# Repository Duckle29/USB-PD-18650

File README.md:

# USB PD 18650

I needed a 12V 5A PSU for my Sequre S60 soldering iron, and I couldn't find any reasonably priced ones, so why not make
my own unreasonably priced one?

This uses an STM32G0 MCU with a TCPP03-M20 protection chip
A MPS programmable buck/boost to provide 5-20V output at up to 5A

The goal is currently to make a complete USB-PD supply with PPS support, but this may be dropped if I don't feel like it when I
figure out how hard it'll be.

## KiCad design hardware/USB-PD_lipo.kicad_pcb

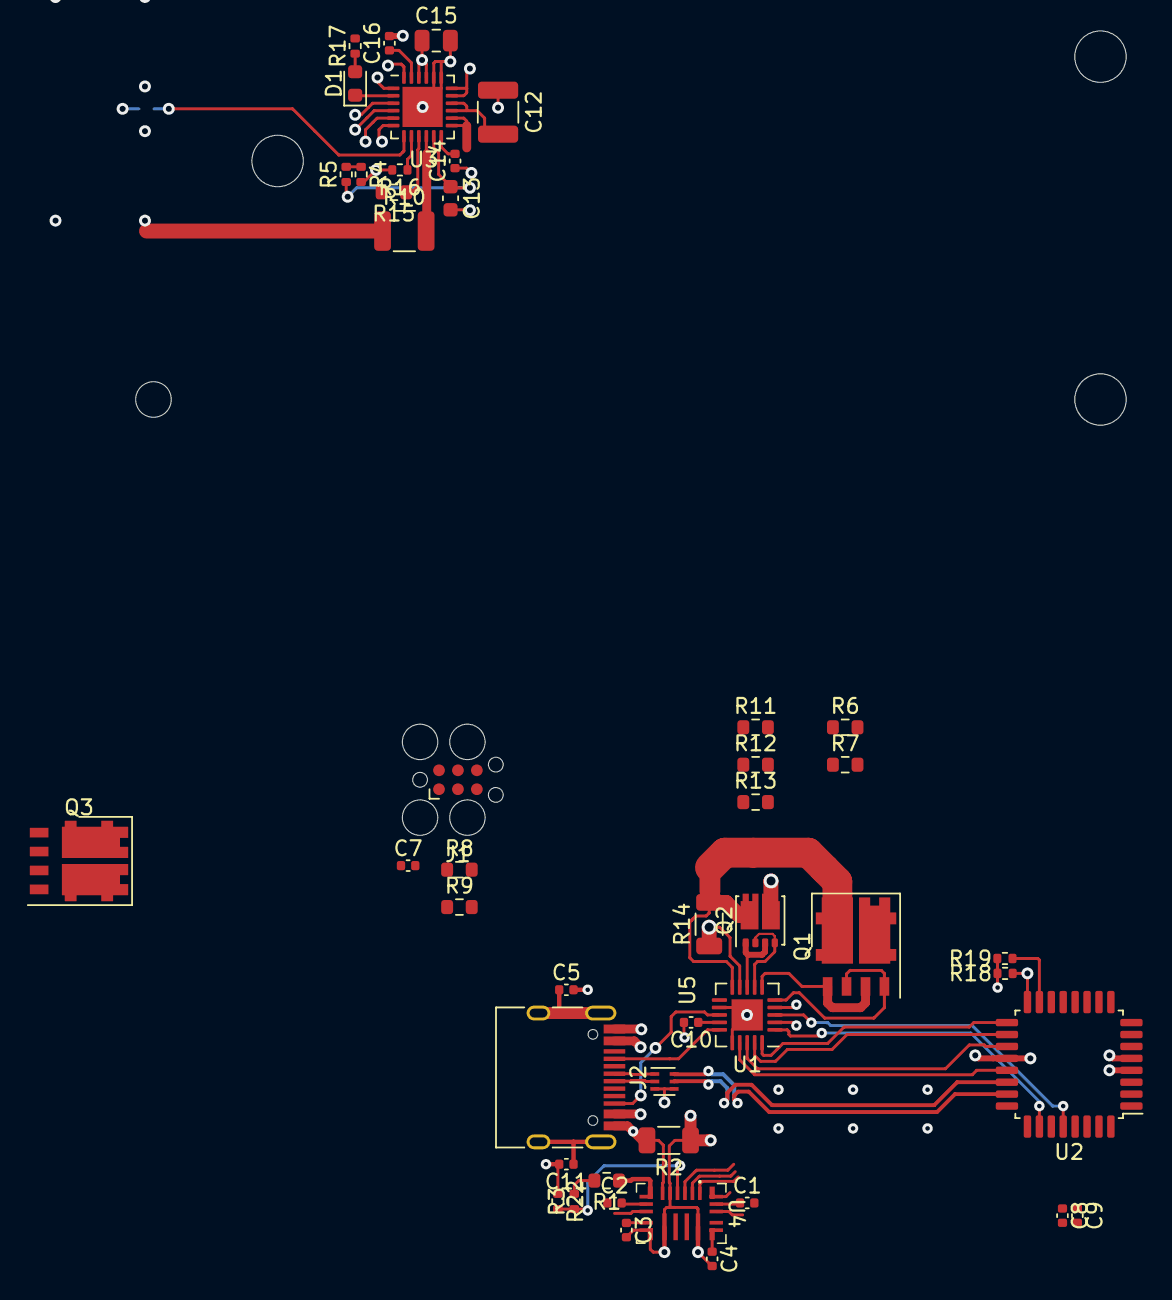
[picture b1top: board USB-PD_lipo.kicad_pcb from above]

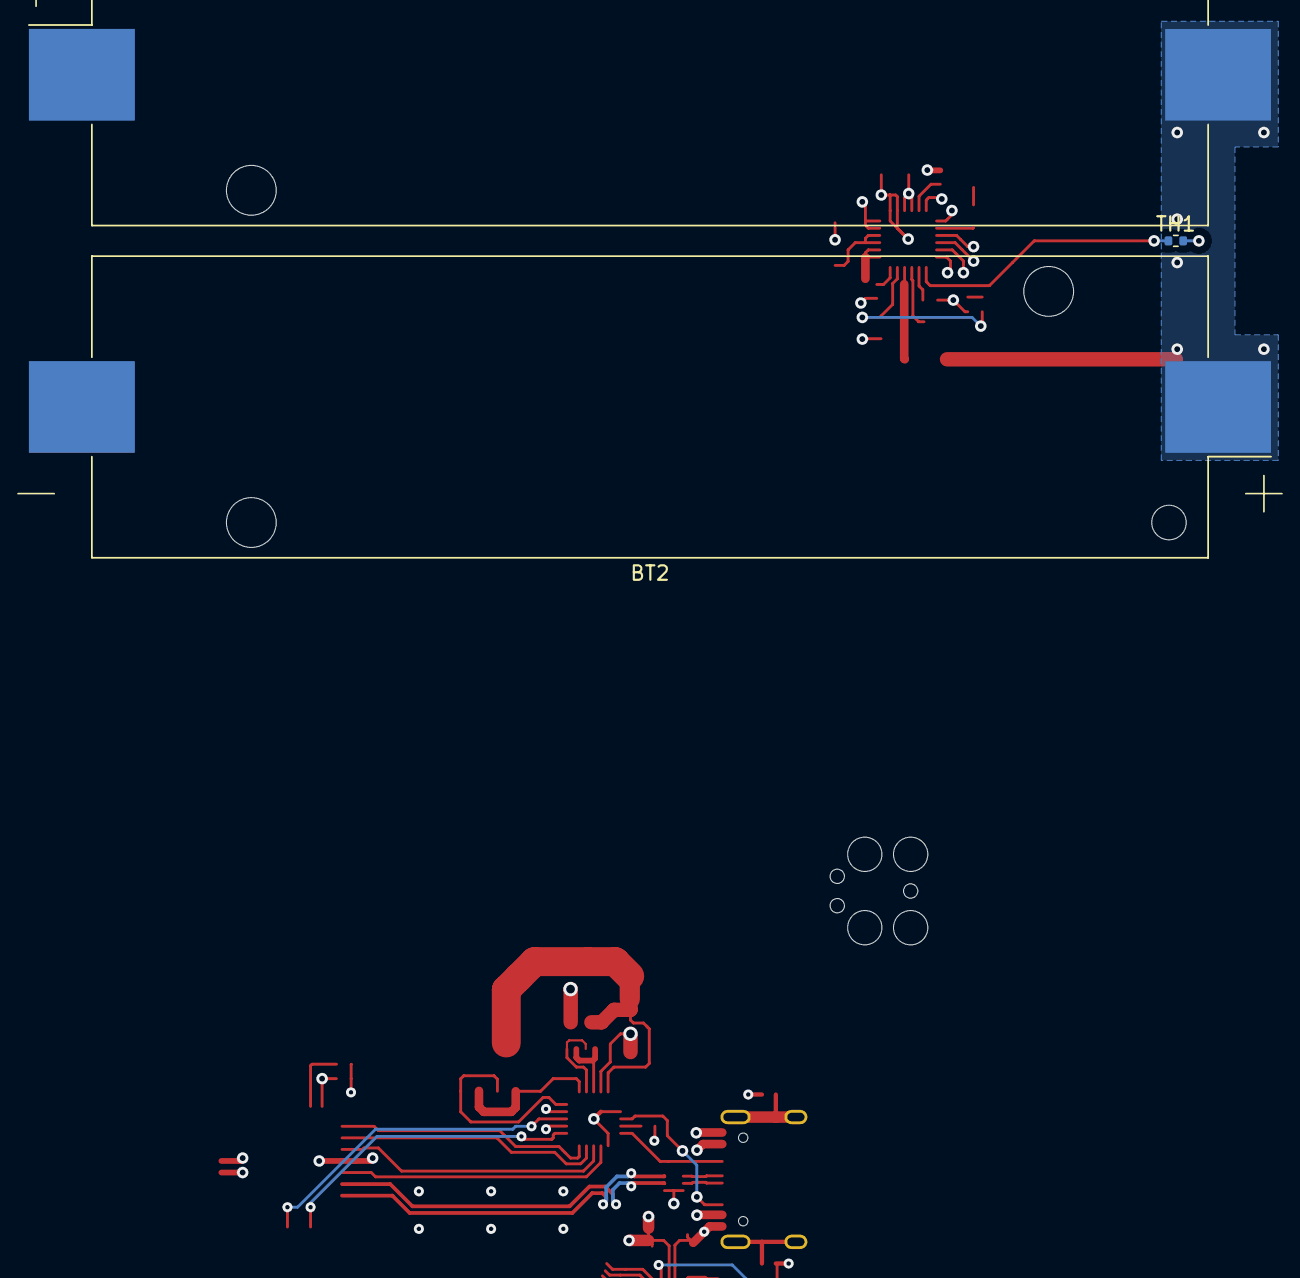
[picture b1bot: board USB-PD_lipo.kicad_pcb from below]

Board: 4 copper layers, 49 parts (3 on the bottom side), 61 nets.

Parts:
BT1, BT2: Battery_Cell; BatteryHolder_Keystone_1042_1x18650
C1, C2: 220nF; C_0402_1005Metric
C3: 1uF; C_0402_1005Metric
C4: 100pF; C_0402_1005Metric
C5, C10, C11: 100nF 50v; C_0402_1005Metric
C7, C8, C9: 100nF; C_0402_1005Metric
C12: 44uF; C_1210_3225Metric
C13: 4u7; C_0603_1608Metric
C14: 47n; C_0402_1005Metric
C15: 10uF; C_0805_2012Metric
C16: 1u; C_0402_1005Metric
D1: LED_Small; LED_0603_1608Metric
J1: TC2030-SWD; Tag-Connect_TC2030-IDC-FP_2x03_P1.27mm_Vertical
J2: USB_C_Receptacle_USB2.0; USB_C_Receptacle_HRO_TYPE-C-31-M-12
Q1, Q3: STL40DN3LLH5; ST_PowerFLAT-6L_5x6mm_P1.27mm
Q2: DMT3020LDV; Diodes_PowerDI3333-8_UXC_3.3x3.3mm_P0.65mm
R1: 3R3; R_0603_1608Metric
R2, R14: 5mR; R_1206_3216Metric
R3: 90k9; R_0402_1005Metric
R4: 30k1; R_0402_1005Metric
R5: 5k23; R_0402_1005Metric
R6, R7, R8, R9, R11: 10k; R_0603_1608Metric
R10: 22R 1W; R_1210_3225Metric
R12, R13: 47k; R_0603_1608Metric
R15: 300R; R_0603_1608Metric
R16: 383R; R_0402_1005Metric
R17: 2k2; R_0402_1005Metric
R18, R19, R22: 10k; R_0402_1005Metric
TH1: 10K beta3435; R_0402_1005Metric
U1: TCPP03-M20; TQFN-20-1EP_4x4mm_P0.5mm_EP2.1x2.1mm
U2: STM32G0C1KETxN; LQFP-32_7x7mm_P0.8mm
U3: BQ25887; QFN-24-1EP_4x4mm_P0.5mm_EP2.7x2.7mm
U4: MP4247; MPS_QFN-20_3x5mm_P0.5mm
U5: ECMF02-2AMX6; ST_UQFN-6L_1.5x1.7mm_Pitch0.5mm

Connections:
+3V3: J1.1 (VCC), R6.1, R7.1, R12.1, R13.1, R17.2, R18.1, R19.1, U1.2 (VCC_{VCONN}), U2.4 (VDD), U2.20 (VDDIO2)
/BMS/CD: U2.30 (PB6), U3.3 (CD)
/BMS/PSEL: U2.31 (PB7), U3.24 (PSEL)
/BMS/SCL: R7.2, U1.18 (SCL), U2.19 (I2C1_SCL), U3.5 (SCL), U4.1 (SCL)
/BMS/SDA: R6.2, U1.17 (SDA), U2.21 (I2C1_SDA), U3.4 (SDA), U4.2 (SDA)
/BMS/VBAT: BT1.1 (+), Q3.6 (D), U3.13 (BAT), U3.14 (BAT), U4.20 (VIN)
/BMS/~INT: R19.2, U2.15 (PB0), U3.6 (~INT)
/BMS/~PG: R18.2, U2.16 (PB1), U3.1 (~PG)
/DC-DC/EN: U2.14 (PA7), U4.17 (EN)
/DC-DC/I_SENS+: J2.A1 (GND), J2.A12 (GND), J2.B1 (GND), J2.B12 (GND), R2.2, U4.6 (ISEN+)
/DC-DC/VOUT: Q1.5 (D), Q3.5 (D), R1.2, R3.2
/DC-DC/~ALERT: U2.13 (PA6), U4.3 (~ALT)
/MCU/CC1: U1.1 (CC1), U2.26 (UCPD2_CC1)
/MCU/CC2: U1.3 (CC2), U2.28 (UCPD2_CC2)
/MCU/SWCLK: J1.4 (SWCLK), U2.25 (SYS_SWCLK)
/MCU/SWDIO: J1.2 (SWDIO), U2.24 (SYS_SWDIO)
/MCU/TCPP_EN: R12.2, U1.20 (EN), U2.17 (PB15)
/MCU/TCPP_sens: R9.2, U1.4 (IANA)
/MCU/USB_D+: U2.23 (USB_DP), U5.6 (D+_out)
/MCU/USB_D-: U2.22 (USB_DM), U5.5 (D-_out)
/MCU/~RST: C7.1, J1.3 (~RESET), U2.6 (PF2)
/MCU/~TCPP_CONNECTION_FLAG: R13.2, U1.19 (FLG_{n}), U2.18 (PA8)
/USB-PD dual role protection/D+: J2.A6 (D+), J2.B6 (D+), U5.1 (D+_in)
/USB-PD dual role protection/D-: J2.A7 (D-), J2.B7 (D-), U5.2 (D-_in)
/USB-PD dual role protection/VBUS: J2.A4 (VBUS), J2.A9 (VBUS), J2.B4 (VBUS), J2.B9 (VBUS), R11.1, R14.1, U1.9 (VBUS_{c})
GND: BT2.2 (-), C3.2, C4.2, C5.2, C7.2, C8.2, C9.2, C10.2, C11.2, C12.2, C13.2, C15.2, C16.2, J1.5 (GND), R2.1, R4.2, R16.2, R22.1, TH1.2, U1.12 (GND), U1.16 (I2C_{ADD}), U1.21 (GND), U2.5 (VSS), U3.19 (GND), U3.20 (GND), U3.25 (EP), U4.5 (ISEN-), U4.11 (AGND), U4.12 (PGND), U4.15 (PGND), U5.3 (GND)
unnamed: BT1.2 (-), BT2.1 (+), R10.1, R15.2
unnamed: C12.1, U3.15 (SNS), U3.16 (SNS)
unnamed: C14.1, U3.17 (SW), U3.18 (SW)
unnamed: C15.1, U3.21 (PMID), U3.22 (PMID)
unnamed: D1.2 (A), R17.1
unnamed: D1.1 (K), U3.2 (STAT)
unnamed: J2.A5 (CC1), U1.15 (CC1_{c})
unnamed: J2.B5 (CC2), U1.13 (CC2_{c})
unnamed: C5.1, C11.1, J2.S1 (SHIELD)
unnamed: Q1.6 (D), Q2.6 (D), R14.2, U1.10 (I_{sense})
unnamed: Q1.2 (G), Q1.4 (G), U1.5 (GDP_{g})
unnamed: Q1.1 (S), Q1.3 (S), U1.6 (GDP_{s})
unnamed: Q2.2 (G), Q2.4 (G), U1.7 (GDC_{g})
unnamed: Q2.1 (S), Q2.3 (S), U1.8 (GDC_{s})
unnamed: Q3.2 (G), U4.18 (HG1)
unnamed: C1.2, Q3.1 (S), U4.14 (SW1)
unnamed: Q3.4 (G), U4.9 (HG2)
unnamed: C2.1, Q3.3 (S), U4.13 (SW2)
unnamed: C10.1, U1.14 (C_{BIAS})
unnamed: R11.2, U1.11 (V_{sense})
unnamed: C8.1, R8.1, U2.11 (ADC1_IN4)
unnamed: C9.1, R9.1, U2.12 (ADC1_IN5)
unnamed: C14.2, U3.12 (BTST)
unnamed: R10.2, U3.10 (CBSET)
unnamed: R16.1, U3.8 (ILIM)
unnamed: R15.1, U3.9 (MID)
unnamed: C13.1, R5.1, U3.11 (REGN)
unnamed: R4.1, R5.2, TH1.1, U3.7 (TS)
unnamed: C1.1, U4.19 (BST1)
unnamed: C2.2, U4.8 (BST2)
unnamed: R3.1, R22.2, U4.4 (FB)
unnamed: C4.1, U4.16 (IMON)
unnamed: C3.1, U4.10 (VCC)
unnamed: R1.1, U4.7 (VOUT)
VBUS: C16.1, Q2.5 (D), U3.23 (VBUS)

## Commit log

2023-05-20 Folderized things
2023-05-23 Added BMS and DC/DC
2023-05-27 Some routing and pinout changes
